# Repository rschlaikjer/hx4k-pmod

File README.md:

# HX4k PMOD Breakout

This repository contains the KiCad hardware design files, flash programming
firmware and some gateware samples for a basic FPGA breakout board based on the
Lattice Ice40 HX4K.

More information about this project can be found
[in this blog post](https://rhye.org/post/fpgas-1-running-on-hardware/).

## Building the hardware

### Prerequisites

- Soldering iron (TS-100 or TS-80 would be fine for this)
- Flux (Massively simplifies the soldering of the QFP packages)
- Fine tweezers (I recommend [Rhino SW-11](https://www.adafruit.com/product/3096) or comparable)
- [Optional] Hot air rework station. The '858D' hot air station is available
from many resellers at reasonable prices, and is more than adequate.

One of the design goals for this board was for it to be feasible to assemble by
hand, using only a soldering iron. To that end, all of the critical
components are leaded packages, and there are no passives smaller than 0805.
For some components (USB type-C connector J4, 12MHz oscillator X1 and RGB LEDs
D1 and U4), a hot air gun may be advantageous, but it is possible to get away
without one.

### Ordering PCBs

If you have done this before, you can clone this repo and then zip up the
gerber fills in the
[hardware/gerber/](https://github.com/rschlaikjer/hx4k-pmod/tree/master/hardware/gerber/)
directory and upload them to your preferred board house.
Alternately, or for convenience, you can
[order this design directly](https://www.pcbway.com/project/shareproject/Lattice_HX4K_FPGA_Breakout.html)
from PCBWay, a budget PCB house with respectable quality and turnaround time.

### Bill of materials

The KiCad design files are fully specified with the manufacturer and DigiKey
part numbers for all components involved. Also included in the `hardware/` folder
is a DigiKey BOM CSV (`digikey_bom.csv`), which can be uploaded
[here](https://www.digikey.com/BOM/) and used to immediately add the necessary
components to an order. Note that the BOM item quantity is for _precisely_ one
unit - I would recommend going through and adding whatever fudge factor you
feel is reasonable to cheaper passives and other parts you want some margin for
error with.

At time of writing, the total cost of the BOM for no more than one board is $37.60.
If you intend to make more than one, the unit price will of course decrease.

### Assembly

I highly recommend printing out the `F.Fab` and `B.Fab` layers of the KiCad
design before getting to work, as these contain a wireframe layout of all the
components, as well as their associated values (pictured on right hand side). I
would also recommend starting with the center of the major component sections
(U1, U3) and working outwards to smaller components, otherwise some of the
decoupling caps near the chips may make it tricky to solder the QFPs.

If you are using a hot air station for assembly, I would recommend applying
flux to the pads, tinning them, placing the component on top and then using the
hot air tool to reflow it into place. I find 350°C to work well for leaded
solder. Be careful not to overheat the LEDs, as the plastic may melt.

# Flashing the microcontroller

Once you have the hardware assembled, you will need to program the onboard
microcontroller. This micro then acts in much the same way as an FTDI FT2232
(but costs significantly less), and once set up allows for

- Writing bitstreams / other data to the onboard flash chip
- Creating a USB serial bridge to the FPGA
- Any other custom logic you want to add. The microcontroller has one hardware
SPI connected directly to the FPGA for end user applications.

To build the firmware, you will need the `arm-none-eabi` GCC toolchain:

    sudo apt install gcc-arm-none-eabi gdb-arm-none-eabi binutils-arm-none-eabi

You should then be able to build the firmware as a normal CMake project:

    # Ensure submodule for libopencm3 is present
    git submodule init
    git submodule update
    # Build
    mkdir programmer_firmware/build
    pushd programmer_firmware/build
    cmake ../
    make -j$(nproc)

To program, it is assumed that you will be using the
[Black Magic Probe](https://1bitsquared.com/products/black-magic-probe)
with a
[TagConnect TC-2050-NL](https://www.tag-connect.com/product/tc2050-idc-nl-050-all)
cable to connect to the programming pads on the board. In this case, after
connecting power to the board through either the USB connector or auxiliary
power connector,  you can
run the cmake target `fpga_programmer_flash` to attach to the microcontroller
and load the firmware. You should see output like the following:

    ross@mjolnir:/h/r/P/G/f/p/build$ make fpga_programmer_flash
    [ 44%] Built target libopencm3
    [100%] Built target fpga_programmer_elf
    Black Magic Probe (Firmware v1.6.1-311-gfbf1963) (Hardware Version 3)

    Available Targets:
    No. Att Driver
     1      STM32F07 M0
    event_loop () at /home/ross/Programming/Github/fpga-swe-1/programmer_firmware/src/main.cpp:87
    87	}
    Loading section .text, size 0x29e4 lma 0x8000000
    Loading section .init_array, size 0x8 lma 0x80029e4
    Loading section .data, size 0x14 lma 0x80029ec
    Start address 0x8001e84, load size 10752
    Transfer rate: 18 KB/sec, 768 bytes/write.
    Section .text, range 0x8000000 -- 0x80029e4: matched.
    Section .init_array, range 0x80029e4 -- 0x80029ec: matched.
    Section .data, range 0x80029ec -- 0x8002a00: matched.
    Kill the program being debugged? (y or n) [answered Y; input not from terminal]
    [100%] Built target fpga_programmer_flash

You should then see the board show up as a USB device, with the default VID:PID
set to a generic test PID:

    ross@mjolnir:/h/r/P/G/f/p/build$ lsusb -d 1209:0001
    Bus 001 Device 106: ID 1209:0001 Generic pid.codes Test PID

You should also notice that it has supplied a new serial device. This serial
port controls the hardware UART on the microcontroller, which is connected
directly to two pins on the FPGA and by default expects a baudrate of 2M.

## Flashing the FPGA

In order to generate bitstreams for the FPGA, you will first need to install
[yosys](https://github.com/YosysHQ/yosys),
[icestorm](http://www.clifford.at/icestorm/)
and
[nextpnr](https://github.com/YosysHQ/nextpnr). Instructions for all of them are
on their respective homepages.

Once these are installed, if you run `make` in the `gateware/` subfolder you
should be able to generate a `top.bin` bitstream of the demo application, which
will blink some lights and act as an echo UART.

In order to upload the bitstream, you will then need to build
[faff](https://github.com/rschlaikjer/faff),
a tool that handles the USB communication necessary to erase and reprogram the
flash through the microcontroller.

Once you have that installed and in your `$PATH`, you can run `make prog` from
the `gateware/` directory and should see it connect and program successfully:

    ross@mjolnir:/h/r/P/G/f/gateware$ make prog
    faff -f top.bin
    Claimed device 1209:0001 with serial 004700254753511120303234
    Flash chip mfgr: 0xef, Device ID: 0x17 Unique ID: 0xe4682c404b163333
    Programming block 0x00020fa0 / 0x00020fbc
    Reading block 0x00020fa0 / 0x00020fbc

Your FPGA should now cycle through some various colours on the RGB LED.

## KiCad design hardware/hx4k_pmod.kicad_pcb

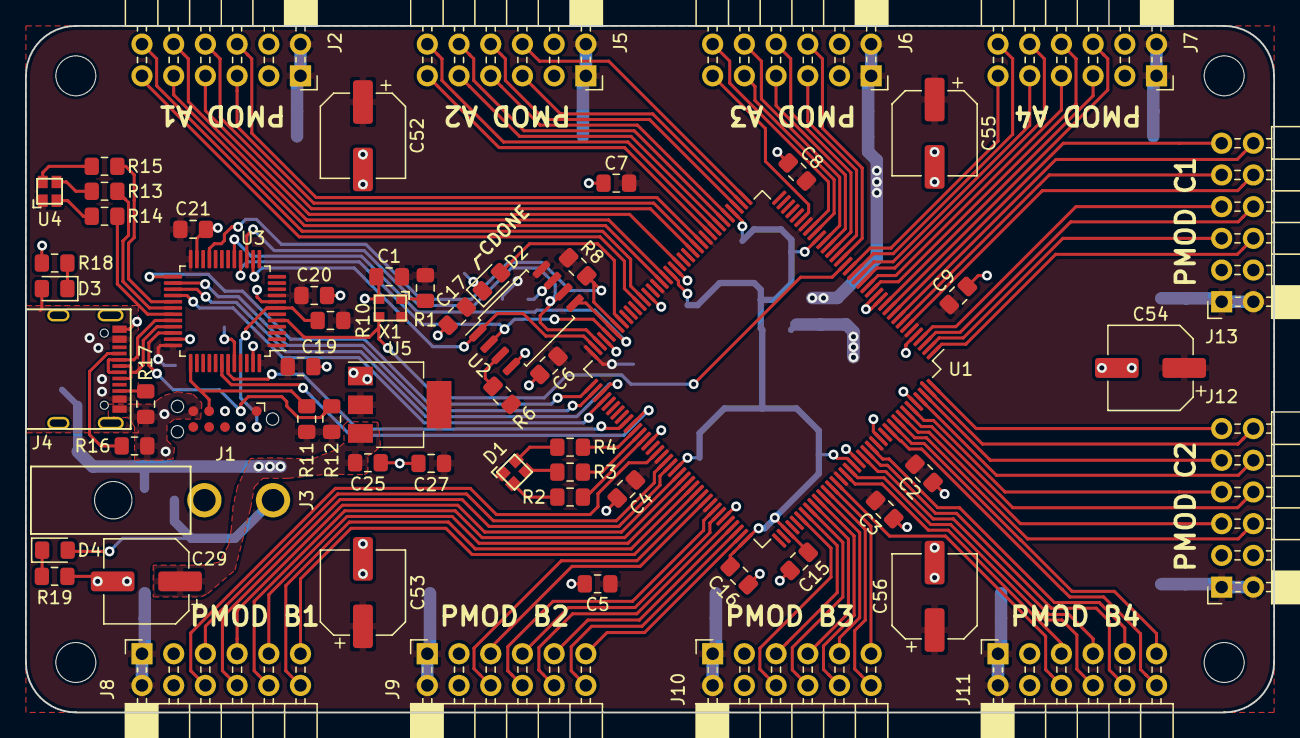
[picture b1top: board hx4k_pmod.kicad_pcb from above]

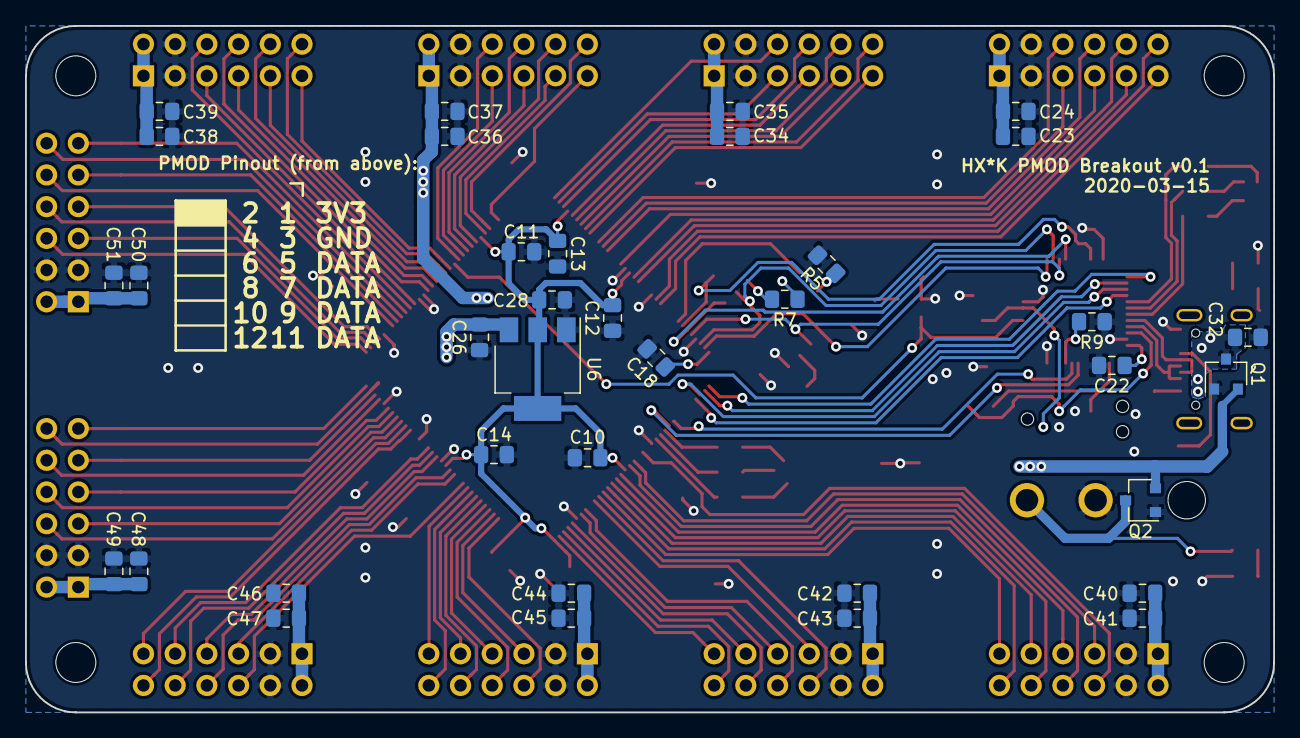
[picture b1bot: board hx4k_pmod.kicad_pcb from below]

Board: 2 copper layers, 100.0 x 55.0 mm, 103 parts (37 on the bottom side), 125 nets.

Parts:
C1, C13, C14, C16, C23, C34, C36, C38, C40, C42, C44, C46, C48, C50: 0.1uF; C_0805_2012Metric_Pad1.15x1.40mm_HandSolder
C2, C4, C6, C8, C25, C26, C27, C28, C32: 10uF; C_0805_2012Metric_Pad1.15x1.40mm_HandSolder
C3, C5, C7, C9, C10, C11, C12, C15, C17, C18, C19, C20, C21, C22, C24, C35, C37, C39, C41, C43, C45, C47, C49, C51: 1uF; C_0805_2012Metric_Pad1.15x1.40mm_HandSolder
C29, C52, C53, C54, C55, C56: 100uF; CP_Elec_6.3x5.8
D1: LED_ABGR; LED_Cree_PLCC4_RGB
D2: LED_BLU; LED_0805_2012Metric_Pad1.15x1.40mm_HandSolder
D3, D4: LED_GRN; LED_0805_2012Metric_Pad1.15x1.40mm_HandSolder
H1, H2, H3, H4: MountingHole; MountingHole_3.2mm_M3
J1: Conn_ARM_JTAG_SWD_10; Tag-Connect_TC2050-IDC-NL_2x05_P1.27mm_Vertical
J2, J5, J6, J7, J8, J9, J10, J11, J12, J13: PMOD; PinSocket_2x06_P2.54mm_Horizontal
J3: Conn_01x02; Conn_Molex_Mini-Fit-JR_2pos_RA_4.2mm
J4: USB_C_Receptacle_USB2.0; Conn_USB_C_Receptacle_GCT_USB4105-GF-A
Q1, Q2: DMG3401LSN-7; SC-59
R1, R6, R7, R8, R9, R10, R11, R12: 10k; R_0805_2012Metric_Pad1.15x1.40mm_HandSolder
R2, R3, R4, R5, R13, R14, R15, R18, R19: 330R; R_0805_2012Metric_Pad1.15x1.40mm_HandSolder
R16, R17: 5.1k; R_0805_2012Metric_Pad1.15x1.40mm_HandSolder
U1: ICE40HX4K-TQ144; TQFP-144_20x20mm_P0.5mm
U2: W25Q128JVS; SOIC-8_5.23x5.23mm_P1.27mm
U3: STM32F070CBTx; LQFP-48_7x7mm_P0.5mm
U4: LED_ABGR; LED_Cree_PLCC4_RGB
U5: AZ1117-3.3; SOT-223-3_TabPin2
U6: AZ1117-1.2; SOT-223-3_TabPin2
U7: ART; fishbox_5mm_600dpi
X1: ECS-2520MV-120; XTAL_OSC_ECS_2520

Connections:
+1V2: C10.2, C11.2, C12.2, C13.2, C14.2, C15.2, C16.1, C28.2, U1.27, U1.40, U1.54, U1.92, U1.108, U1.111, U1.126, U6.2
+3V3: C1.2, C2.2, C3.1, C4.2, C5.1, C6.2, C7.1, C8.2, C9.1, C17.1, C18.1, C19.1, C20.1, C21.1, C22.1, C23.1, C24.1, C26.2, C27.2, C34.1, C35.1, C36.1, C37.1, C38.1, C39.1, C40.1, C41.1, C42.1, C43.1, C44.1, C45.1, C46.1, C47.1, C48.1, C49.1, C50.1, C51.1, C52.1, C53.1, C54.1, C55.1, C56.1, D1.1, J1.1, J2.1, J2.2, J5.1, J5.2, J6.1, J6.2, J7.1, J7.2, J8.1, J8.2, J9.1, J9.2, J10.1, J10.2, J11.1, J11.2, J12.1, J12.2, J13.1, J13.2, R1.2, R6.2, R7.1, R8.1, R10.1, R11.1, R12.1, U1.6, U1.30, U1.46, U1.57, U1.72, U1.89, U1.100, U1.123, U1.131, U2.8, U3.1, U3.9, U3.24, U3.36, U3.48, U4.1, U5.2, U6.3, X1.4
+5V: C25.2, C29.1, Q1.2, Q2.2, U5.3
/12MHZ_OSC: U1.21, U3.5, X1.3
/FPGA_FLASH_MISO: U1.68, U2.2, U3.16
/FPGA_FLASH_MOSI: U1.67, U2.5, U3.17
/FPGA_FLASH_SCK: U1.70, U2.6, U3.15
/FPGA_SLAVE_SPI_MISO: U1.75, U3.27
/FPGA_SLAVE_SPI_MOSI: U1.76, U3.28
/FPGA_SLAVE_SPI_SCK: U1.74, U3.26
/FPGA_UART_RX: U1.82, U3.42
/FPGA_UART_TX: U1.81, U3.43
/MCU_USB_D+: J4.A6, J4.B6, U3.33
/MCU_USB_D-: J4.A7, J4.B7, U3.32
/Sheet5E6E5EAE/LED_BLUE: R4.2, U1.83
/Sheet5E6E5EAE/LED_GREEN: R3.2, U1.84
/Sheet5E6E5EAE/LED_RED: R2.2, U1.85
/Sheet5E6E5EAE/PMOD_A1_D0: J2.11, U1.61
/Sheet5E6E5EAE/PMOD_A1_D1: J2.9, U1.56
/Sheet5E6E5EAE/PMOD_A1_D2: J2.7, U1.52
/Sheet5E6E5EAE/PMOD_A1_D3: J2.5, U1.48
/Sheet5E6E5EAE/PMOD_A1_D4: J2.12, U1.60
/Sheet5E6E5EAE/PMOD_A1_D5: J2.10, U1.55
/Sheet5E6E5EAE/PMOD_A1_D6: J2.8, U1.49
/Sheet5E6E5EAE/PMOD_A1_D7: J2.6, U1.47
/Sheet5E6E5EAE/PMOD_A2_D0: J5.11, U1.45
/Sheet5E6E5EAE/PMOD_A2_D1: J5.9, U1.43
/Sheet5E6E5EAE/PMOD_A2_D2: J5.7, U1.41
/Sheet5E6E5EAE/PMOD_A2_D3: J5.5, U1.38
/Sheet5E6E5EAE/PMOD_A2_D4: J5.12, U1.44
/Sheet5E6E5EAE/PMOD_A2_D5: J5.10, U1.42
/Sheet5E6E5EAE/PMOD_A2_D6: J5.8, U1.39
/Sheet5E6E5EAE/PMOD_A2_D7: J5.6, U1.37
/Sheet5E6E5EAE/PMOD_A3_D0: J6.11, U1.31
/Sheet5E6E5EAE/PMOD_A3_D1: J6.9, U1.28
/Sheet5E6E5EAE/PMOD_A3_D2: J6.7, U1.25
/Sheet5E6E5EAE/PMOD_A3_D3: J6.5, U1.23
/Sheet5E6E5EAE/PMOD_A3_D4: J6.12, U1.29
/Sheet5E6E5EAE/PMOD_A3_D5: J6.10, U1.26
/Sheet5E6E5EAE/PMOD_A3_D6: J6.8, U1.24
/Sheet5E6E5EAE/PMOD_A3_D7: J6.6, U1.22
/Sheet5E6E5EAE/PMOD_A4_D0: J7.11, U1.20
/Sheet5E6E5EAE/PMOD_A4_D1: J7.9, U1.18
/Sheet5E6E5EAE/PMOD_A4_D2: J7.7, U1.16
/Sheet5E6E5EAE/PMOD_A4_D3: J7.5, U1.12
/Sheet5E6E5EAE/PMOD_A4_D4: J7.12, U1.19
/Sheet5E6E5EAE/PMOD_A4_D5: J7.10, U1.17
/Sheet5E6E5EAE/PMOD_A4_D6: J7.8, U1.15
/Sheet5E6E5EAE/PMOD_A4_D7: J7.6, U1.11
/Sheet5E6E5EAE/PMOD_B1_D0: J8.11, U1.97
/Sheet5E6E5EAE/PMOD_B1_D1: J8.9, U1.95
/Sheet5E6E5EAE/PMOD_B1_D2: J8.7, U1.93
/Sheet5E6E5EAE/PMOD_B1_D3: J8.5, U1.90
/Sheet5E6E5EAE/PMOD_B1_D4: J8.12, U1.96
/Sheet5E6E5EAE/PMOD_B1_D5: J8.10, U1.94
/Sheet5E6E5EAE/PMOD_B1_D6: J8.8, U1.91
/Sheet5E6E5EAE/PMOD_B1_D7: J8.6, U1.88
/Sheet5E6E5EAE/PMOD_B2_D0: J9.11, U1.107
/Sheet5E6E5EAE/PMOD_B2_D1: J9.9, U1.105
/Sheet5E6E5EAE/PMOD_B2_D2: J9.7, U1.102
/Sheet5E6E5EAE/PMOD_B2_D3: J9.5, U1.99
/Sheet5E6E5EAE/PMOD_B2_D4: J9.12, U1.106
/Sheet5E6E5EAE/PMOD_B2_D5: J9.10, U1.104
/Sheet5E6E5EAE/PMOD_B2_D6: J9.8, U1.101
/Sheet5E6E5EAE/PMOD_B2_D7: J9.6, U1.98
/Sheet5E6E5EAE/PMOD_B3_D0: J10.11, U1.121
/Sheet5E6E5EAE/PMOD_B3_D1: J10.9, U1.119
/Sheet5E6E5EAE/PMOD_B3_D2: J10.7, U1.117
/Sheet5E6E5EAE/PMOD_B3_D3: J10.5, U1.115
/Sheet5E6E5EAE/PMOD_B3_D4: J10.12, U1.120
/Sheet5E6E5EAE/PMOD_B3_D5: J10.10, U1.118
/Sheet5E6E5EAE/PMOD_B3_D6: J10.8, U1.116
/Sheet5E6E5EAE/PMOD_B3_D7: J10.6, U1.114
/Sheet5E6E5EAE/PMOD_B4_D0: J11.11, U1.135
/Sheet5E6E5EAE/PMOD_B4_D1: J11.9, U1.130
/Sheet5E6E5EAE/PMOD_B4_D2: J11.7, U1.128
/Sheet5E6E5EAE/PMOD_B4_D3: J11.5, U1.124
/Sheet5E6E5EAE/PMOD_B4_D4: J11.12, U1.134
/Sheet5E6E5EAE/PMOD_B4_D5: J11.10, U1.129
/Sheet5E6E5EAE/PMOD_B4_D6: J11.8, U1.125
/Sheet5E6E5EAE/PMOD_B4_D7: J11.6, U1.122
/Sheet5E6E5EAE/PMOD_C1_D0: J13.11, U1.10
/Sheet5E6E5EAE/PMOD_C1_D1: J13.9, U1.8
/Sheet5E6E5EAE/PMOD_C1_D2: J13.7, U1.4
/Sheet5E6E5EAE/PMOD_C1_D3: J13.5, U1.2
/Sheet5E6E5EAE/PMOD_C1_D4: J13.12, U1.9
/Sheet5E6E5EAE/PMOD_C1_D5: J13.10, U1.7
/Sheet5E6E5EAE/PMOD_C1_D6: J13.8, U1.3
/Sheet5E6E5EAE/PMOD_C1_D7: J13.6, U1.1
/Sheet5E6E5EAE/PMOD_C2_D0: J12.11, U1.144
/Sheet5E6E5EAE/PMOD_C2_D1: J12.9, U1.142
/Sheet5E6E5EAE/PMOD_C2_D2: J12.7, U1.139
/Sheet5E6E5EAE/PMOD_C2_D3: J12.5, U1.137
/Sheet5E6E5EAE/PMOD_C2_D4: J12.12, U1.143
/Sheet5E6E5EAE/PMOD_C2_D5: J12.10, U1.141
/Sheet5E6E5EAE/PMOD_C2_D6: J12.8, U1.138
/Sheet5E6E5EAE/PMOD_C2_D7: J12.6, U1.136
/Sheet5E6E65DF/VUSB: C32.1, D3.2, J4.A4, J4.B4, Q1.3
/Sheet5E6E6210/SWCLK: J1.4, R11.2, U3.37
/Sheet5E6E6210/SWDIO: J1.2, R12.2, U3.34
/Sheet5E6E6210/TIM1_CH1: R15.2, U3.29
/Sheet5E6E6210/TIM1_CH2: R13.2, U3.30
/Sheet5E6E6210/TIM1_CH3: R14.2, U3.31
/Sheet5E6E6210/~MCU_RESET: J1.10, R10.2, U3.7
/~FPGA_FLASH_CS: U1.71, U2.1, U3.14
/~FPGA_RESET: R8.2, U1.66, U3.21
/~FPGA_SLAVE_SPI_CS: U1.73, U3.25
GND: C1.1, C2.1, C3.2, C4.1, C5.2, C6.1, C7.2, C8.1, C9.2, C10.1, C11.1, C12.1, C13.1, C14.1, C15.1, C16.2, C17.2, C18.2, C19.2, C20.2, C21.2, C22.2, C23.2, C24.2, C25.1, C26.1, C27.1, C28.1, C29.2, C32.2, C34.2, C35.2, C36.2, C37.2, C38.2, C39.2, C40.2, C41.2, C42.2, C43.2, C44.2, C45.2, C46.2, C47.2, C48.2, C49.2, C50.2, C51.2, C52.2, C53.2, C54.2, C55.2, C56.2, J1.3, J1.5, J1.9, J2.3, J2.4, J3.1, J4.A1, J4.B1, J5.3, J5.4, J6.3, J6.4, J7.3, J7.4, J8.3, J8.4, J9.3, J9.4, J10.3, J10.4, J11.3, J11.4, J12.3, J12.4, J13.3, J13.4, Q1.1, Q2.1, R5.2, R9.1, R16.1, R17.1, R18.2, R19.2, U1.5, U1.13, U1.14, U1.53, U1.59, U1.69, U1.86, U1.103, U1.127, U1.132, U1.140, U2.4, U3.8, U3.23, U3.35, U3.47, U5.1, U6.1, X1.2
unnamed: D1.2, R4.1
unnamed: D1.3, R3.1
unnamed: D1.4, R2.1
unnamed: D2.1, R5.1
unnamed: D2.2, U1.65
unnamed: D3.1, R18.1
unnamed: D4.1, R19.1
unnamed: D4.2, J3.2, Q2.3
unnamed: J4.A5, R16.2
unnamed: J4.B5, R17.2
unnamed: R1.1, X1.1
unnamed: R6.1, U2.3
unnamed: R7.2, U2.7
unnamed: R9.2, U3.44
unnamed: R13.1, U4.3
unnamed: R14.1, U4.4
unnamed: R15.1, U4.2

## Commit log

2020-03-28 Hardware design
2020-03-28 Vendor opencm3
2020-03-28 Barebones firmware init
2020-03-28 Config, structure
2020-03-28 RGB, timer, fpga reset init
2020-03-28 USB device shows up
2020-03-28 Watchdog
2020-03-28 Had the USB endpoints backwards
2020-03-28 Sketch of usb protocol
2020-03-28 Start fleshing out protocol, add SPI
2020-03-28 Allow manual LED setting
2020-03-28 Minimal cmakelists
2020-03-28 Getting device by vid/pid/serial works
2020-03-29 Throw away CDC data to prevent it clogging pipes
2020-03-29 Opening file to program, sending basic commands
2020-03-29 Back and forth comms
2020-03-29 Verify reset
2020-03-29 Reading flash ID
2020-03-29 Read unique ID
2020-03-29 Erase functions
2020-03-29 Able to program flash
2020-03-29 Actually release reset
2020-03-29 Print error reasons
2020-03-29 Initial demo verilog
2020-03-29 Wire up uart pipe
2020-03-29 README and images
2020-03-29 Elaborate on assembly a bit
2020-03-29 Add rest of the PCF file
2020-03-30 Backlink
2020-04-09 Forgot to fill in ordering
2020-04-12 Move blink gateware to subfolder
2020-04-12 Use condensed format for PMOD wires
2020-08-21 Fix placement error for A2[7]
2020-09-08 Permissive license
